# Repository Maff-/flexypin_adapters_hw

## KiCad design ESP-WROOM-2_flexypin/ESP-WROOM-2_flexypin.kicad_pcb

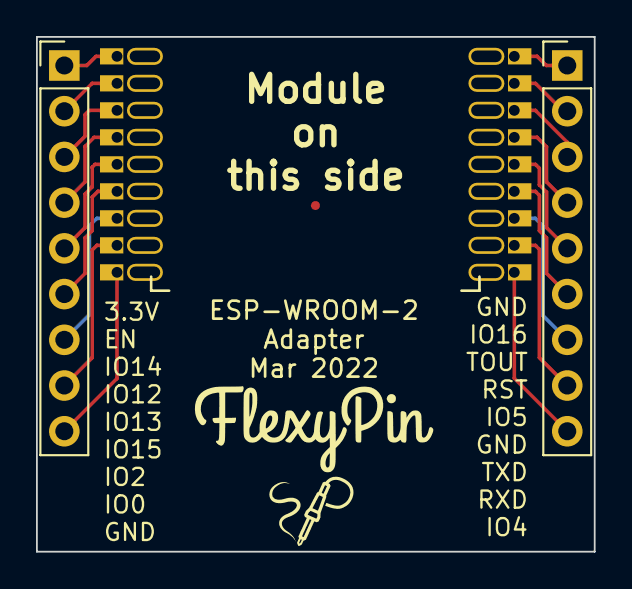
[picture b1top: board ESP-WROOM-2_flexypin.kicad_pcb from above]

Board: 2 copper layers, 31.0 x 28.6 mm, 20 parts (0 on the bottom side), 18 nets.

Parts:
J1, J22: Conn_01x09; PinHeader_1x09_P2.54mm_Vertical
J2, J3, J4, J5, J6, J7, J8, J9, J10, J11, J12, J13, J14, J15, J16, J17, J18, J23: Conn_01x01; FlexyPin_1x01

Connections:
/3.3V: J1.1, J2.1
/EN: J1.2, J3.1
/GND: J1.9, J23.1
/IO0: J11.1, J22.1
/IO1: J12.1, J22.2
/IO2: J13.1, J22.3
/IO3: J14.1, J22.4
/IO4: J1.3, J4.1
/IO5: J1.4, J5.1
/IO6: J1.5, J7.1
/IO7: J1.6, J8.1
/IO8: J1.7, J9.1
/IO9: J1.8, J10.1
/IO10: J6.1, J22.9
/IO18: J16.1, J22.6
/IO19: J15.1, J22.5
/RXD: J18.1, J22.8
/TXD: J17.1, J22.7

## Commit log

2022-04-06 Create ESP-WROOM-2(D) adapter based on ESP-32-WROOM
